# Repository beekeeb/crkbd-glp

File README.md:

# Corne GLP (Gateron Low Profile)

The Corne GLP (Gateron Low Profile) is a variant of the Corne keyboard, originally created by [foostan](https://github.com/foostan/crkbd "foostan"). It supports Gateron low-profile key switches (KS-27 and KS-33). The original Corne firmware can be used with this keyboard.

## Photos

## Bill of Materials (BOM)
### Required

| Name | Count | Remarks |
|:-|:-|:-|
| PCB | 1 set | |
| Top plate | 2 sheets | 1.2mm thick |
| Bottom plate | 2 sheets | |
| OLED cover | 2 sheets | |
| Pro Micro or equivalent | 2 |  |
| TRRS jack | 2 | |
| Reset switch | 2 | |
| Diodes | 42 | SMD Only (SOD-123 Package) |
| Gateron Low Profile Hotswap Sockets | 42 |  |
| Key switches | 42 | Only compatible with Gateron KS-33 / KS-27 |
| Keycaps | 42 pieces | 1u 40 pcs, 1.5u 2 pcs [Keycaps Comparison](https://showcase.beekeeb.com/the-keycaps-of-gateron-low-profile-key-switches-and-kailh-choc-v1-key-switch/) |
| Spacer M2 5mm | 10 pieces | For Case assembly |
| Spacer M2 9mm | 4 pieces | For OLED cover |
| Screw M2 4mm | 28 screws | |
| Rubber feet | 8 pieces | |
| TRRS (4 poles) cable | 1 |  |
| Micro USB or USB-C cable | 1 | Avoid charge-only cables |

### Optional

| Name | Count | Remarks |
|:-|:-|:-|
| OLED module | 2 | |
| SK6812MINI-E | 42 | LEDs for Backlight |
| WS2812B | 12 | LEDs for Undergrow |
| Microcontroller/OLED Sockets | 1 |  |
| Microcontroller Pins | 48 | Alternative: Diode/Resistor legs |
| OLED Headers | 1 | Soldered to OLED module |

## Plates
It is compatible with Corne v3 top and bottom plates.
* [Corne Top / Bottom Plates](https://github.com/foostan/crkbd/tree/main/plates/pcb)

## Ordering Parts

[DIY kits / Prebuilt Keyboards](https://shop.beekeeb.com/product/corne-glp-kit/) are available at https://beekeeb.shop.

## External Libraries
* [https://github.com/siderakb/key-switches.pretty](https://github.com/siderakb/key-switches.pretty)
* [https://github.com/foostan/kbd](https://github.com/foostan/kbd)

## More Information
* [A great doc about Gateron Low Profile switches writen by Rafael Yumagulov](https://ergonautkb.github.io/docs/switches/gateron-low-profile/)
* [More photo of Corne GLP](https://showcase.beekeeb.com/corne-glp/)
* [Keycaps for Gateron Low Profile Key Switches](https://showcase.beekeeb.com/the-keycaps-of-gateron-low-profile-key-switches-and-kailh-choc-v1-key-switch/)

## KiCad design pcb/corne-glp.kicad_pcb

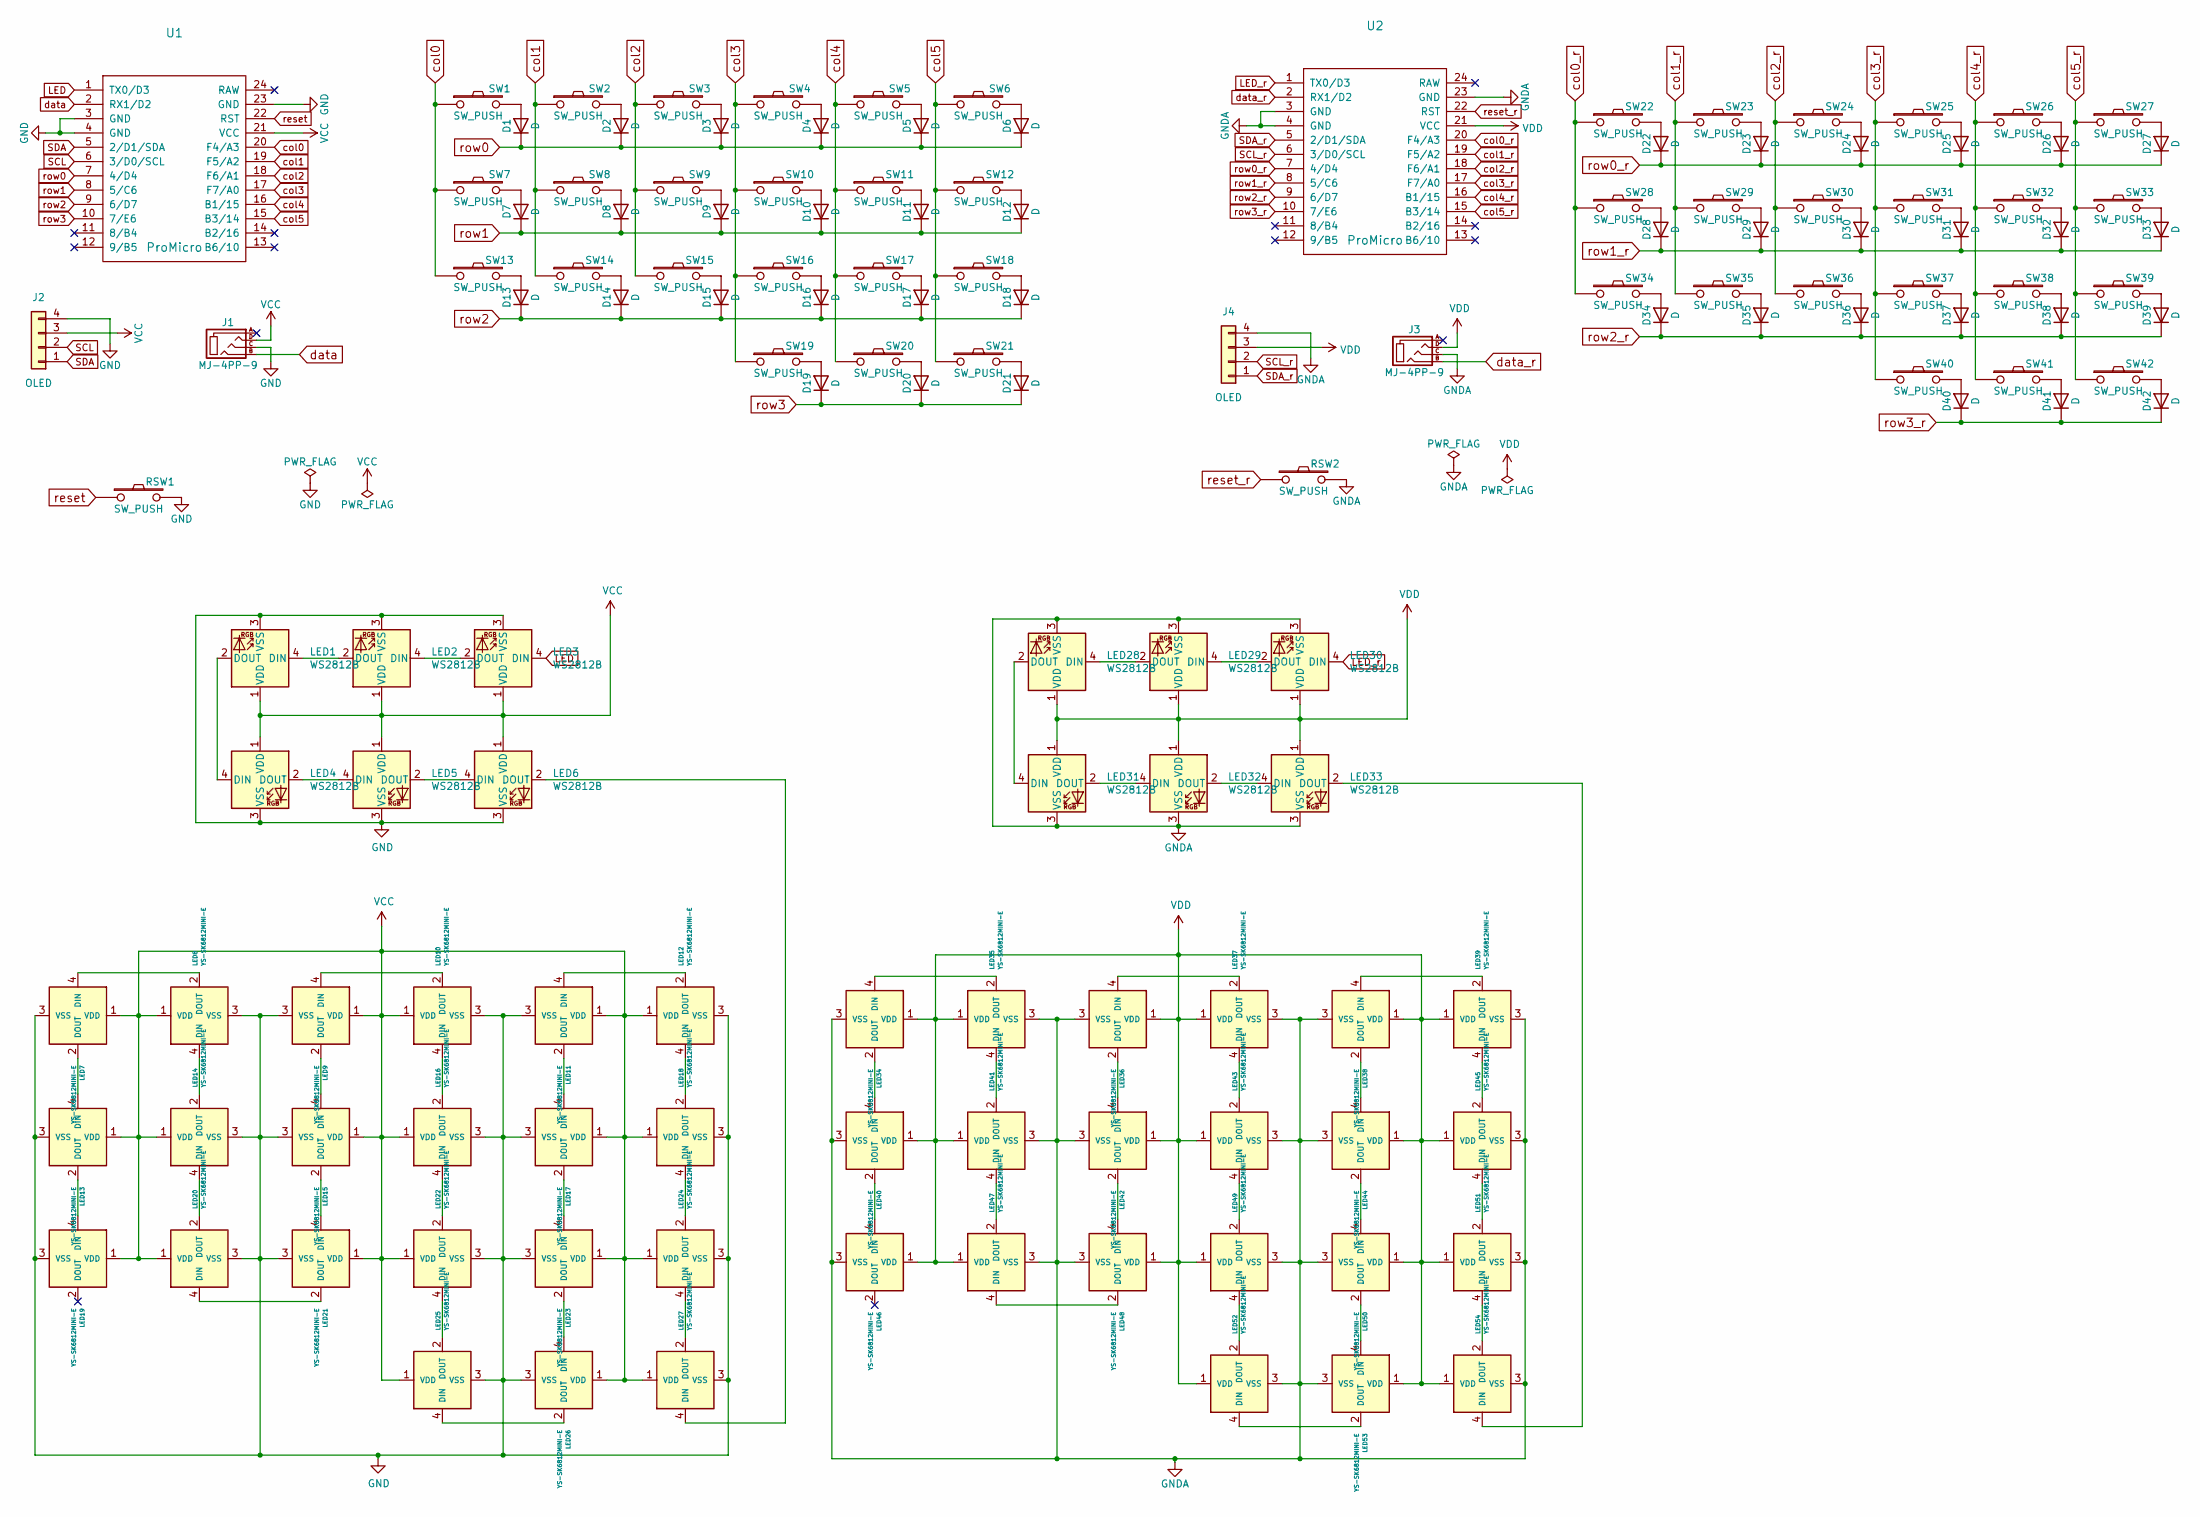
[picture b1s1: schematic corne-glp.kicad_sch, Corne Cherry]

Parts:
D1, D2, D3, D4, D5, D6, D7, D8, D9, D10, D11, D12, D13, D14, D15, D16, D17, D18, D19, D20, D21, D22, D23, D24, D25, D26, D27, D28, D29, D30, D31, D32, D33, D34, D35, D36, D37, D38, D39, D40, D41, D42: D; D3_SMD_v2
J1, J3: MJ-4PP-9; MJ-4PP-9_1side
J2, J4: OLED; OLED_1side
LED1, LED2, LED3, LED4, LED5, LED6, LED28, LED29, LED30, LED31, LED32, LED33: WS2812B; LED_WS2812B_PLCC4_5.0x5.0mm_P3.2mm
LED7, LED8, LED9, LED10, LED11, LED12, LED13, LED14, LED15, LED16, LED17, LED18, LED19, LED20, LED21, LED22, LED23, LED24, LED25, LED26, LED27, LED34, LED35, LED36, LED37, LED38, LED39, LED40, LED41, LED42, LED43, LED44, LED45, LED46, LED47, LED48, LED49, LED50, LED51, LED52, LED53, LED54: YS-SK6812MINI-E
RSW1, RSW2: SW_PUSH; ResetSW_1side
SW1, SW2, SW3, SW4, SW5, SW6, SW7, SW8, SW9, SW10, SW11, SW12, SW13, SW14, SW15, SW16, SW17, SW18, SW19, SW20, SW22, SW23, SW24, SW25, SW26, SW27, SW28, SW29, SW30, SW31, SW32, SW33, SW34, SW35, SW36, SW37, SW38, SW39, SW40, SW41: SW_PUSH; CherryMX_Hotswap
SW21, SW42: SW_PUSH; CherryMX_Hotswap_1.5u
U1, U2: ProMicro; ProMicro_v3

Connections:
GND: J1.C, J2.4, LED1.3 (VSS), LED2.3 (VSS), LED3.3 (VSS), LED4.3 (VSS), LED5.3 (VSS), LED6.3 (VSS), LED7.3 (VSS), LED8.3 (VSS), LED9.3 (VSS), LED10.3 (VSS), LED11.3 (VSS), LED12.3 (VSS), LED13.3 (VSS), LED14.3 (VSS), LED15.3 (VSS), LED16.3 (VSS), LED17.3 (VSS), LED18.3 (VSS), LED19.3 (VSS), LED20.3 (VSS), LED21.3 (VSS), LED22.3 (VSS), LED23.3 (VSS), LED24.3 (VSS), LED25.3 (VSS), LED26.3 (VSS), LED27.3 (VSS), RSW1.2, U1.3 (GND), U1.4 (GND), U1.23 (GND)
LED: LED3.4 (DIN), U1.1 (TX0/D3)
LED_r: LED30.4 (DIN), U2.1 (TX0/D3)
unnamed: D1.2 (A), SW1.2
unnamed: D2.2 (A), SW2.2
unnamed: D3.2 (A), SW3.2
unnamed: D4.2 (A), SW4.2
unnamed: D5.2 (A), SW5.2
unnamed: D6.2 (A), SW6.2
unnamed: D7.2 (A), SW7.2
unnamed: D8.2 (A), SW8.2
unnamed: D9.2 (A), SW9.2
unnamed: D10.2 (A), SW10.2
unnamed: D11.2 (A), SW11.2
unnamed: D12.2 (A), SW12.2
unnamed: D13.2 (A), SW13.2
unnamed: D14.2 (A), SW14.2
unnamed: D15.2 (A), SW15.2
unnamed: D16.2 (A), SW16.2
unnamed: D17.2 (A), SW17.2
unnamed: D18.2 (A), SW18.2
unnamed: D19.2 (A), SW19.2
unnamed: D20.2 (A), SW20.2
unnamed: D21.2 (A), SW21.2
unnamed: D22.2 (A), SW22.2
unnamed: D23.2 (A), SW23.2
unnamed: D24.2 (A), SW24.2
unnamed: D25.2 (A), SW25.2
unnamed: D26.2 (A), SW26.2
unnamed: D27.2 (A), SW27.2
unnamed: D28.2 (A), SW28.2
unnamed: D29.2 (A), SW29.2
unnamed: D30.2 (A), SW30.2
unnamed: D31.2 (A), SW31.2
unnamed: D32.2 (A), SW32.2
unnamed: D33.2 (A), SW33.2
unnamed: D34.2 (A), SW34.2
unnamed: D35.2 (A), SW35.2
unnamed: D36.2 (A), SW36.2
unnamed: D37.2 (A), SW37.2
unnamed: D38.2 (A), SW38.2
unnamed: D39.2 (A), SW39.2
unnamed: D40.2 (A), SW40.2
unnamed: D41.2 (A), SW41.2
unnamed: D42.2 (A), SW42.2
unnamed: LED1.2 (DOUT), LED4.4 (DIN)
unnamed: LED1.4 (DIN), LED2.2 (DOUT)
unnamed: LED2.4 (DIN), LED3.2 (DOUT)
unnamed: LED4.2 (DOUT), LED5.4 (DIN)
unnamed: LED5.2 (DOUT), LED6.4 (DIN)
unnamed: LED7.4 (DIN), LED8.2 (DOUT)
unnamed: LED9.4 (DIN), LED10.2 (DOUT)
unnamed: LED10.4 (DIN), LED16.2 (DOUT)
unnamed: LED11.2 (DOUT), LED17.4 (DIN)
unnamed: LED11.4 (DIN), LED12.2 (DOUT)
unnamed: LED12.4 (DIN), LED18.2 (DOUT)
unnamed: LED13.2 (DOUT), LED19.4 (DIN)
unnamed: LED7.2 (DOUT), LED13.4 (DIN)
unnamed: LED8.4 (DIN), LED14.2 (DOUT)
unnamed: LED14.4 (DIN), LED20.2 (DOUT)
unnamed: LED15.2 (DOUT), LED21.4 (DIN)
unnamed: LED9.2 (DOUT), LED15.4 (DIN)
unnamed: LED16.4 (DIN), LED22.2 (DOUT)
unnamed: LED17.2 (DOUT), LED23.4 (DIN)
unnamed: LED18.4 (DIN), LED24.2 (DOUT)
unnamed: LED20.4 (DIN), LED21.2 (DOUT)
unnamed: LED22.4 (DIN), LED25.2 (DOUT)
unnamed: LED23.2 (DOUT), LED26.4 (DIN)
unnamed: LED24.4 (DIN), LED27.2 (DOUT)
unnamed: LED25.4 (DIN), LED26.2 (DOUT)
unnamed: LED6.2 (DOUT), LED27.4 (DIN)
unnamed: LED28.2 (DOUT), LED31.4 (DIN)
unnamed: LED28.4 (DIN), LED29.2 (DOUT)
unnamed: LED29.4 (DIN), LED30.2 (DOUT)
unnamed: LED31.2 (DOUT), LED32.4 (DIN)
unnamed: LED32.2 (DOUT), LED33.4 (DIN)
unnamed: LED33.2 (DOUT), LED54.4 (DIN)
unnamed: LED34.2 (DOUT), LED40.4 (DIN)
unnamed: LED34.4 (DIN), LED35.2 (DOUT)
unnamed: LED35.4 (DIN), LED41.2 (DOUT)
unnamed: LED36.2 (DOUT), LED42.4 (DIN)
unnamed: LED36.4 (DIN), LED37.2 (DOUT)
unnamed: LED37.4 (DIN), LED43.2 (DOUT)
unnamed: LED38.2 (DOUT), LED44.4 (DIN)
unnamed: LED38.4 (DIN), LED39.2 (DOUT)
unnamed: LED39.4 (DIN), LED45.2 (DOUT)
unnamed: LED40.2 (DOUT), LED46.4 (DIN)
unnamed: LED41.4 (DIN), LED47.2 (DOUT)
unnamed: LED42.2 (DOUT), LED48.4 (DIN)
unnamed: LED43.4 (DIN), LED49.2 (DOUT)
unnamed: LED44.2 (DOUT), LED50.4 (DIN)
unnamed: LED45.4 (DIN), LED51.2 (DOUT)
unnamed: LED47.4 (DIN), LED48.2 (DOUT)
unnamed: LED49.4 (DIN), LED52.2 (DOUT)
unnamed: LED50.2 (DOUT), LED53.4 (DIN)
unnamed: LED51.4 (DIN), LED54.2 (DOUT)
unnamed: LED52.4 (DIN), LED53.2 (DOUT)
SCL: J2.2, U1.6 (3/D0/SCL)
SDA: J2.1, U1.5 (2/D1/SDA)
VCC: J1.D, J2.3, LED1.1 (VDD), LED2.1 (VDD), LED3.1 (VDD), LED4.1 (VDD), LED5.1 (VDD), LED6.1 (VDD), LED7.1 (VDD), LED8.1 (VDD), LED9.1 (VDD), LED10.1 (VDD), LED11.1 (VDD), LED12.1 (VDD), LED13.1 (VDD), LED14.1 (VDD), LED15.1 (VDD), LED16.1 (VDD), LED17.1 (VDD), LED18.1 (VDD), LED19.1 (VDD), LED20.1 (VDD), LED21.1 (VDD), LED22.1 (VDD), LED23.1 (VDD), LED24.1 (VDD), LED25.1 (VDD), LED26.1 (VDD), LED27.1 (VDD), U1.21 (VCC)
col0: SW1.1, SW7.1, SW13.1, U1.20 (F4/A3)
col0_r: SW22.1, SW28.1, SW34.1, U2.20 (F4/A3)
col1: SW2.1, SW8.1, SW14.1, U1.19 (F5/A2)
col1_r: SW23.1, SW29.1, SW35.1, U2.19 (F5/A2)
col2: SW3.1, SW9.1, SW15.1, U1.18 (F6/A1)
col2_r: SW24.1, SW30.1, SW36.1, U2.18 (F6/A1)
col3: SW4.1, SW10.1, SW16.1, SW19.1, U1.17 (F7/A0)
col3_r: SW25.1, SW31.1, SW37.1, SW40.1, U2.17 (F7/A0)
col4: SW5.1, SW11.1, SW17.1, SW20.1, U1.16 (B1/15)
col4_r: SW26.1, SW32.1, SW38.1, SW41.1, U2.16 (B1/15)
col5: SW6.1, SW12.1, SW18.1, SW21.1, U1.15 (B3/14)
col5_r: SW27.1, SW33.1, SW39.1, SW42.1, U2.15 (B3/14)
data: J1.B, U1.2 (RX1/D2)
data_r: J3.B, U2.2 (RX1/D2)
reset: RSW1.1, U1.22 (RST)
reset_r: RSW2.1, U2.22 (RST)
row0: D1.1 (K), D2.1 (K), D3.1 (K), D4.1 (K), D5.1 (K), D6.1 (K), U1.7 (4/D4)
row0_r: D22.1 (K), D23.1 (K), D24.1 (K), D25.1 (K), D26.1 (K), D27.1 (K), U2.7 (4/D4)
row1: D7.1 (K), D8.1 (K), D9.1 (K), D10.1 (K), D11.1 (K), D12.1 (K), U1.8 (5/C6)
row1_r: D28.1 (K), D29.1 (K), D30.1 (K), D31.1 (K), D32.1 (K), D33.1 (K), U2.8 (5/C6)
row2: D13.1 (K), D14.1 (K), D15.1 (K), D16.1 (K), D17.1 (K), D18.1 (K), U1.9 (6/D7)
row2_r: D34.1 (K), D35.1 (K), D36.1 (K), D37.1 (K), D38.1 (K), D39.1 (K), U2.9 (6/D7)
row3: D19.1 (K), D20.1 (K), D21.1 (K), U1.10 (7/E6)
row3_r: D40.1 (K), D41.1 (K), D42.1 (K), U2.10 (7/E6)

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
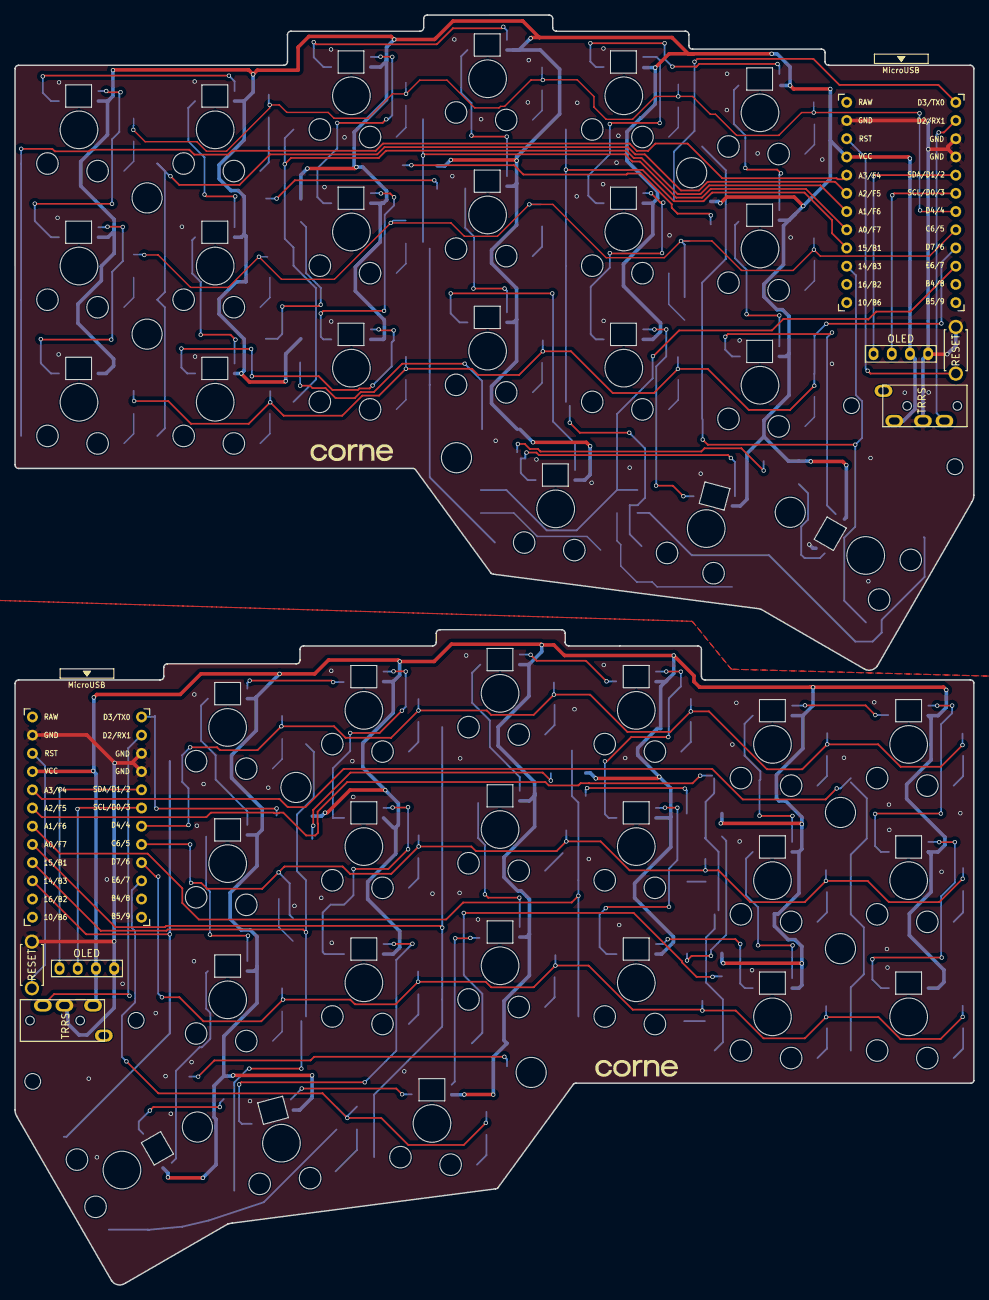
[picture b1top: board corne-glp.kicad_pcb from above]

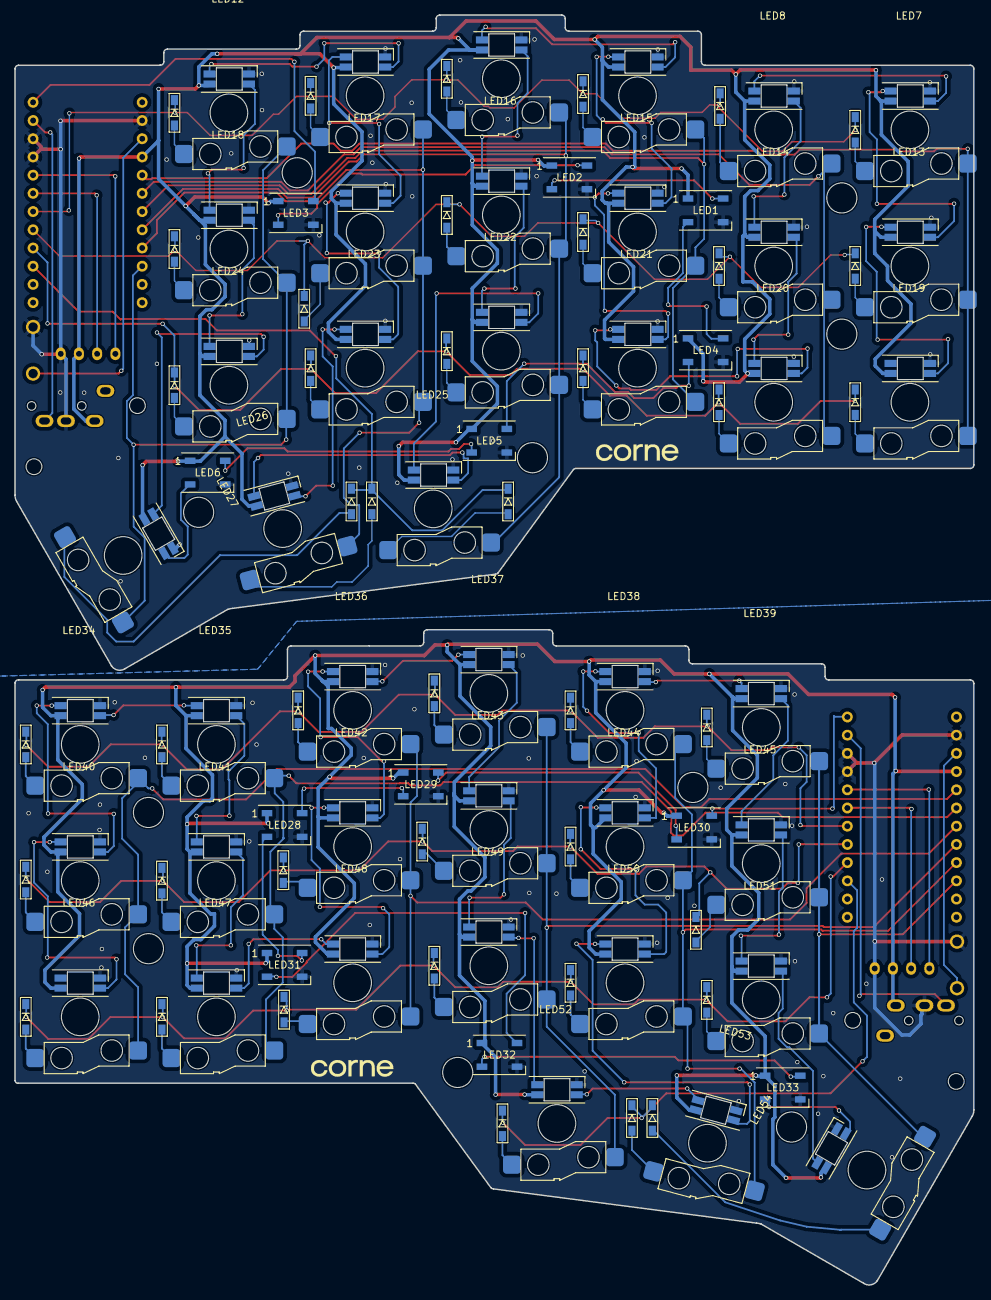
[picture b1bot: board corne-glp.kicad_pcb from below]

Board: 2 copper layers, 133.8 x 177.1 mm, 160 parts (103 on the bottom side), 128 nets.

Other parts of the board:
h1, h3, h4, h5, h6, h7, h8, h9, h10, h11, h12, h13, h14, h15: Val**; M2_HOLE_v2

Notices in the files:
README.md:
License: MIT
